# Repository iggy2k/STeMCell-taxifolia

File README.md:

# STeMCell-taxifolia
 STeMCell 1.0.0 but with STM32F401RCT6. Same functionality (almost), but for 5$ less per board.

Original STeMCell made by https://github.com/megamind4089

To use: https://megamind4089.github.io/STeMCell/

Changed nothing except the STM, positioning and silkscreens (still no on-board protections).

Haven't purchased yet, but it should work.

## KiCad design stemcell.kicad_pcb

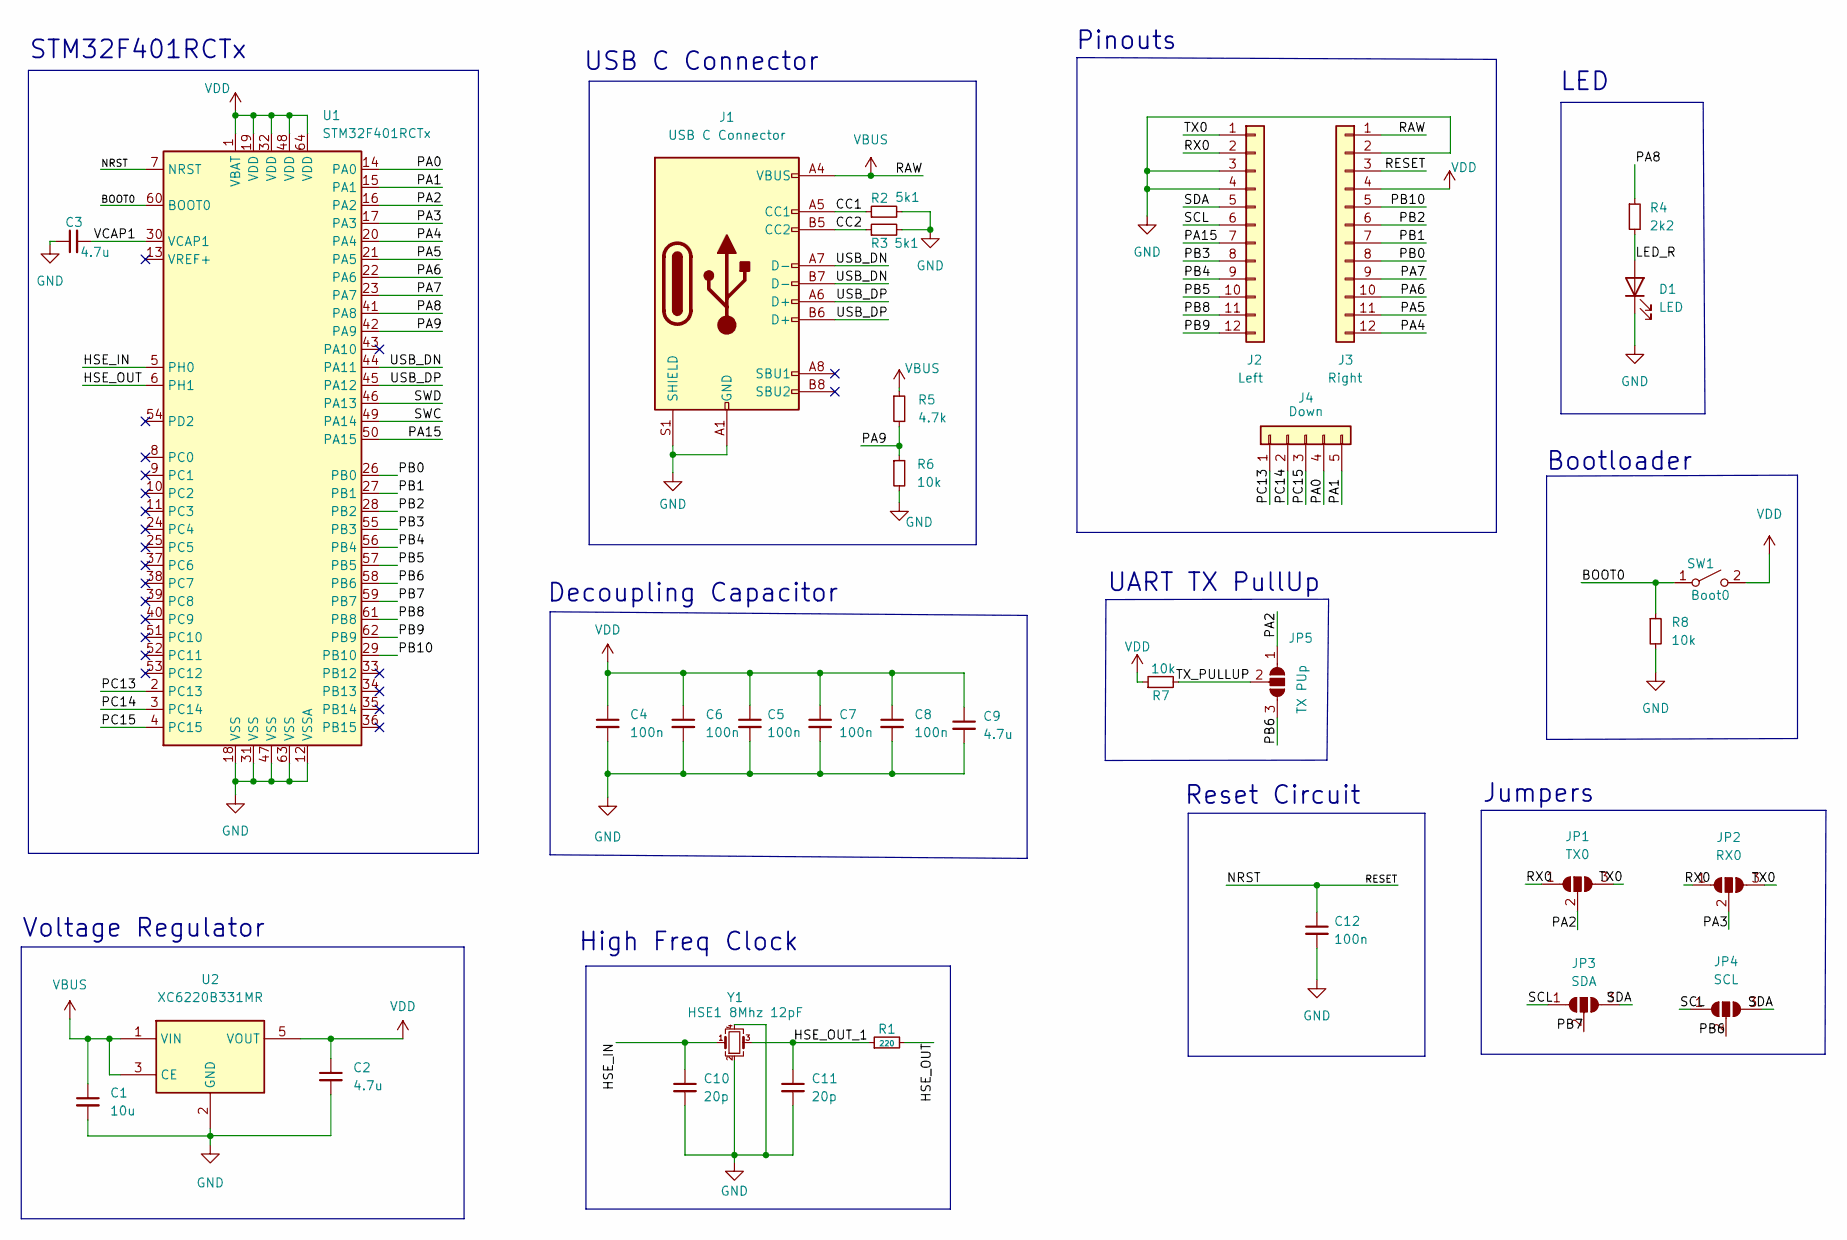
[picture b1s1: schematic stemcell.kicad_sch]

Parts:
C1: 10u; C_0402_1005Metric
C2, C3, C9: 4.7u; C_0402_1005Metric
C4, C5, C6, C7, C8, C12: 100n; C_0402_1005Metric
C10, C11: 20p; C_0402_1005Metric
D1: LED; LED_0603_1608Metric
J1: USB C Connector; USB-C-C168688
J2: Left; Pins_x12
J3: Right; Pins_x12
J4: Down; Pins_x05_Castellated
JP1: TX0; SOLDER_JUMPER_3
JP2: RX0; SOLDER_JUMPER_3
JP3: SDA; SOLDER_JUMPER_3
JP4: SCL; SOLDER_JUMPER_3
JP5: TX PUp; SOLDER_JUMPER_3
R1: 220; R_0402_1005Metric
R2, R3: 5k1; R_0402_1005Metric
R4: 2k2; R_0402_1005Metric
R5: 4.7k; R_0402_1005Metric
R6, R7, R8: 10k; R_0402_1005Metric
SW1: Boot0; SW_SPST_CK_KXT3
U1: STM32F401RCTx; QFP50P1200X1200X160-64N
U2: XC6220B331MR; SOT-23-5
Y1: HSE1 8Mhz 12pF; Crystal_SMD_3225-4Pin_3.2x2.5mm

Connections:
/BOOT0: R8.1, SW1.1 (A), U1.60 (BOOT0)
/CC1: J1.A5 (CC1), R2.1
/CC2: J1.B5 (CC2), R3.1
/HSE_IN: C10.1, U1.5 (PH0), Y1.1
/HSE_OUT: R1.2, U1.6 (PH1)
/HSE_OUT_1: C11.1, R1.1, Y1.3
/LED_R: D1.2 (A), R4.2
/NRST: C12.1, J3.3, U1.7 (NRST)
/PA0: J4.4, U1.14 (PA0)
/PA1: J4.5, U1.15 (PA1)
/PA2: JP1.2 (C), JP5.1 (A), U1.16 (PA2)
/PA3: JP2.2 (C), U1.17 (PA3)
/PA4: J3.12, U1.20 (PA4)
/PA5: J3.11, U1.21 (PA5)
/PA6: J3.10, U1.22 (PA6)
/PA7: J3.9, U1.23 (PA7)
/PA8: R4.1, U1.41 (PA8)
/PA9: R5.2, R6.1, U1.42 (PA9)
/PA15: J2.7, U1.50 (PA15)
/PB0: J3.8, U1.26 (PB0)
/PB1: J3.7, U1.27 (PB1)
/PB2: J3.6, U1.28 (PB2)
/PB3: J2.8, U1.55 (PB3)
/PB4: J2.9, U1.56 (PB4)
/PB5: J2.10, U1.57 (PB5)
/PB6: JP4.2 (C), JP5.3 (B), U1.58 (PB6)
/PB7: JP3.2 (C), U1.59 (PB7)
/PB8: J2.11, U1.61 (PB8)
/PB9: J2.12, U1.62 (PB9)
/PB10: J3.5, U1.29 (PB10)
/PC13: J4.1, U1.2 (PC13)
/PC14: J4.2, U1.3 (PC14)
/PC15: J4.3, U1.4 (PC15)
/RX0: J2.2, JP1.1 (A), JP2.1 (A)
/SCL: J2.6, JP3.1 (A), JP4.1 (A)
/SDA: J2.5, JP3.3 (B), JP4.3 (B)
/SWC: U1.49 (PA14)
/SWD: U1.46 (PA13)
/TX0: J2.1, JP1.3 (B), JP2.3 (B)
/TX_PULLUP: JP5.2 (C), R7.2
/USB_DN: J1.A7 (D-), J1.B7 (D-), U1.44 (PA11)
/USB_DP: J1.A6 (D+), J1.B6 (D+), U1.45 (PA12)
/VCAP1: C3.2, U1.30 (VCAP1)
GND: C1.2, C2.2, C3.1, C4.2, C5.2, C6.2, C7.2, C8.2, C9.2, C10.2, C11.2, C12.2, D1.1 (K), J1.A1 (GND), J1.A12 (GND), J1.B1 (GND), J1.B12 (GND), J1.S1 (SHIELD), J2.3, J2.4, J3.2, R2.2, R3.2, R6.2, R8.2, U1.12 (VSSA), U1.18 (VSS), U1.31 (VSS), U1.47 (VSS), U1.63 (VSS), U2.2 (GND), Y1.2, Y1.4
VBUS: C1.1, J1.A4 (VBUS), J1.A9 (VBUS), J1.B4 (VBUS), J1.B9 (VBUS), J3.1, R5.1, U2.1 (VIN), U2.3 (CE)
VDD: C2.1, C4.1, C5.1, C6.1, C7.1, C8.1, C9.1, J3.4, R7.1, SW1.2 (B), U1.1 (VBAT), U1.19 (VDD), U1.32 (VDD), U1.48 (VDD), U1.64 (VDD), U2.5 (VOUT)

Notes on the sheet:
Jumpers
Decoupling Capacitor
STM32F401RCTx
Reset Circuit
Voltage Regulator
LED
High Freq Clock
Bootloader
UART TX PullUp
USB C Connector
Pinouts

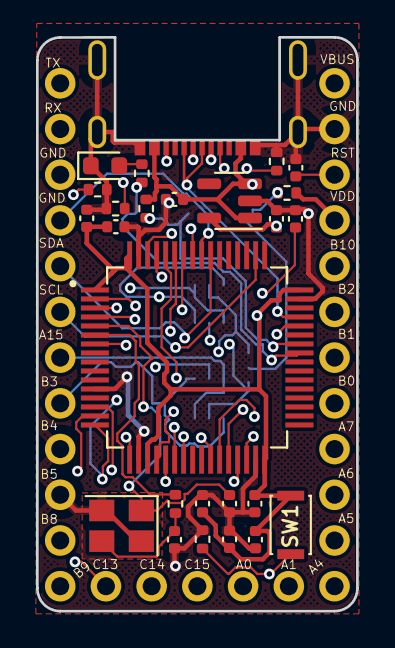
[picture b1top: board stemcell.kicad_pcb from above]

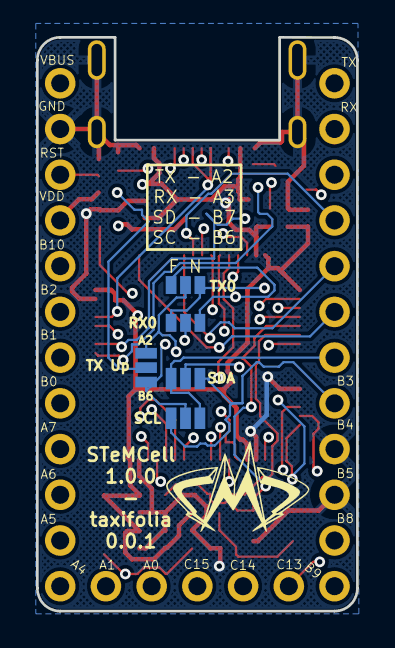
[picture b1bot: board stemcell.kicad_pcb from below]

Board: 4 copper layers, 17.8 x 31.9 mm, 34 parts (5 on the bottom side), 44 nets.

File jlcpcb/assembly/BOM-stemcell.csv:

Comment,Designator,Footprint,LCSC
100n,"C12,C4,C5,C6,C7,C8",C_0402_1005Metric,C1525
10u,C1,C_0402_1005Metric,C15525
20p,"C10,C11",C_0402_1005Metric,C1554
4.7u,"C2,C3,C9",C_0402_1005Metric,C23733
220,R1,R_0402_1005Metric,C25091
10k,"R6,R7,R8",R_0402_1005Metric,C25744
2k2,R4,R_0402_1005Metric,C25879
4.7k,R5,R_0402_1005Metric,C25900
5k1,"R2,R3",R_0402_1005Metric,C25905
USB C Connector,J1,USB-C-C168688,C2681552
HSE1 8Mhz 12pF,Y1,Crystal_SMD_3225-4Pin_3.2x2.5mm,C2682775
Boot0,SW1,SW_SPST_CK_KXT3,C319433
LED,D1,LED_0603_1608Metric,C72041
STM32F401RCTx,U1,QFP50P1200X1200X160-64N,C74524
XC6220B331MR,U2,SOT-23-5,C86534

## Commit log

2022-06-23 Initial Commit
    Everything is ready for purchase/assembly.
2022-06-23 Render and description.
2022-06-23 Move via out of the crystal zone.
    Regenerated the gerbers.
2022-06-23 Moved capacitors out of the way of the pins
    Moved logo back to the back silkscreen.
